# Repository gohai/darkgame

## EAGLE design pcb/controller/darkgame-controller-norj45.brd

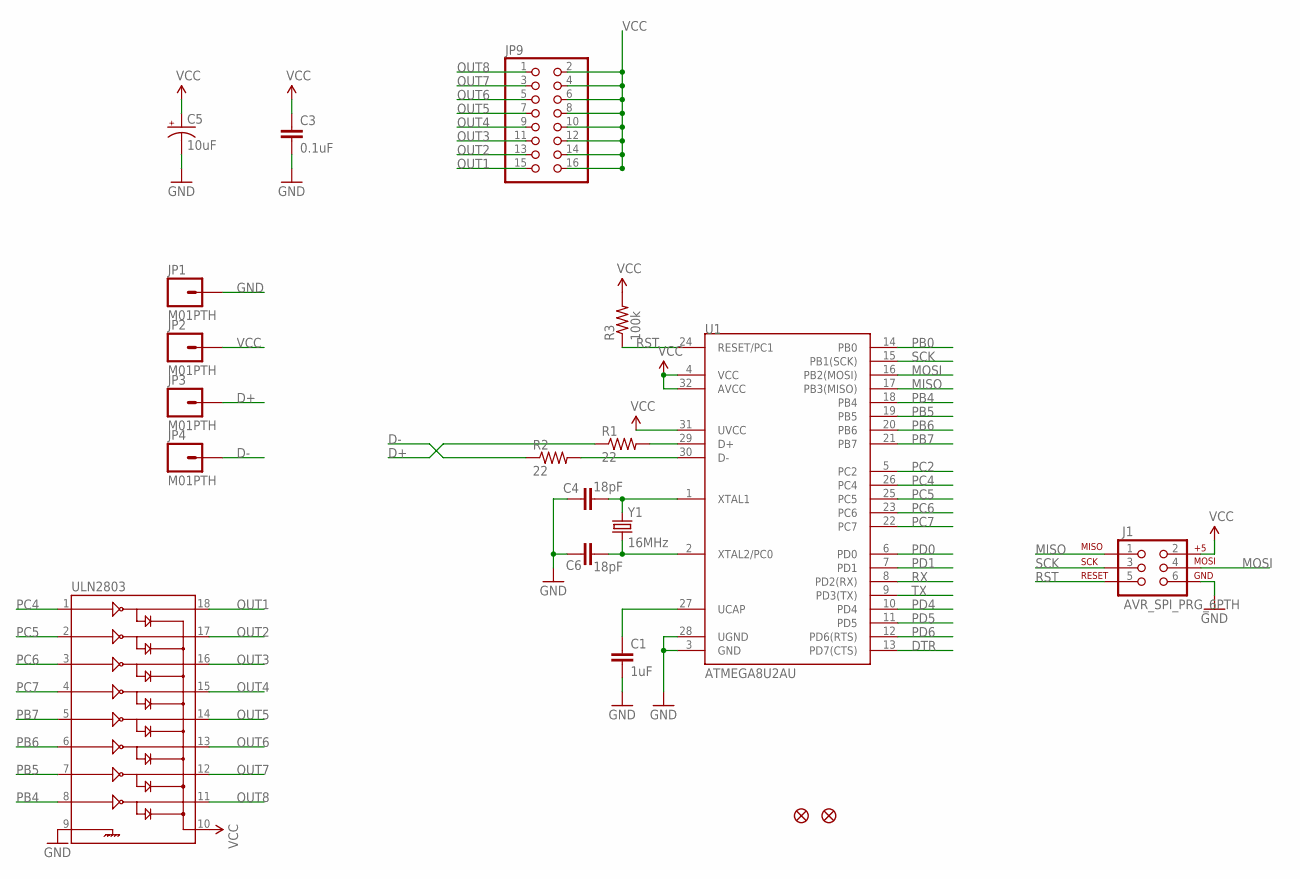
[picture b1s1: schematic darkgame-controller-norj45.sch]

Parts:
C1: 1uF; 0805
C3: 0.1uF; 0805
C4, C6: 18pF; 0805
C5: 10uF; EIA3216
J1: AVR_SPI_PRG_6PTH; 2X3
JP1, JP2, JP3, JP4: M01PTH; 1X01
JP6, JP7: FIDUCIAL1X2; FIDUCIAL-1X2
JP9: PINHD-2X8; 2X08
R1, R2: 22; 0805
R3: 100k; 0805
U1: ATMEGA8U2AU; TQFP32-08
ULN2803: ULN2803SOICW; SO18L
Y1: 16MHz; CRYSTAL-SMD-5X3

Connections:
D+: JP3.1, R1.1
D-: JP4.1, R2.1
DTR: U1.13 (PD7(CTS))
GND: C1.2, C3.2, C4.2, C5.C (-), C6.2, J1.6, JP1.1, U1.3 (GND), U1.28 (UGND), ULN2803.9
MISO: J1.1, U1.17 (PB3(MISO))
MOSI: J1.4, U1.16 (PB2(MOSI))
unnamed: R1.2, U1.29 (D+)
unnamed: R2.2, U1.30 (D-)
unnamed: C4.1, U1.1 (XTAL1), Y1.3 (2)
unnamed: C6.1, U1.2 (XTAL2/PC0), Y1.1
unnamed: C1.1, U1.27 (UCAP)
OUT1: JP9.15, ULN2803.18
OUT2: JP9.13, ULN2803.17
OUT3: JP9.11, ULN2803.16
OUT4: JP9.9, ULN2803.15
OUT5: JP9.7, ULN2803.14
OUT6: JP9.5, ULN2803.13
OUT7: JP9.3, ULN2803.12
OUT8: JP9.1, ULN2803.11
PB0: U1.14 (PB0)
PB4: U1.18 (PB4), ULN2803.8
PB5: U1.19 (PB5), ULN2803.7
PB6: U1.20 (PB6), ULN2803.6
PB7: U1.21 (PB7), ULN2803.5
PC2: U1.5 (PC2)
PC4: U1.26 (PC4), ULN2803.1
PC5: U1.25 (PC5), ULN2803.2
PC6: U1.23 (PC6), ULN2803.3
PC7: U1.22 (PC7), ULN2803.4
PD0: U1.6 (PD0)
PD1: U1.7 (PD1)
PD4: U1.10 (PD4)
PD5: U1.11 (PD5)
PD6: U1.12 (PD6(RTS))
RST: J1.5, R3.1, U1.24 (RESET/PC1)
RX: U1.8 (PD2(RX))
SCK: J1.3, U1.15 (PB1(SCK))
TX: U1.9 (PD3(TX))
VCC: C3.1, C5.A (+), J1.2, JP2.1, JP9.2, JP9.4, JP9.6, JP9.8, JP9.10, JP9.12, JP9.14, JP9.16, R3.2, U1.4 (VCC), U1.31 (UVCC), U1.32 (AVCC), ULN2803.10

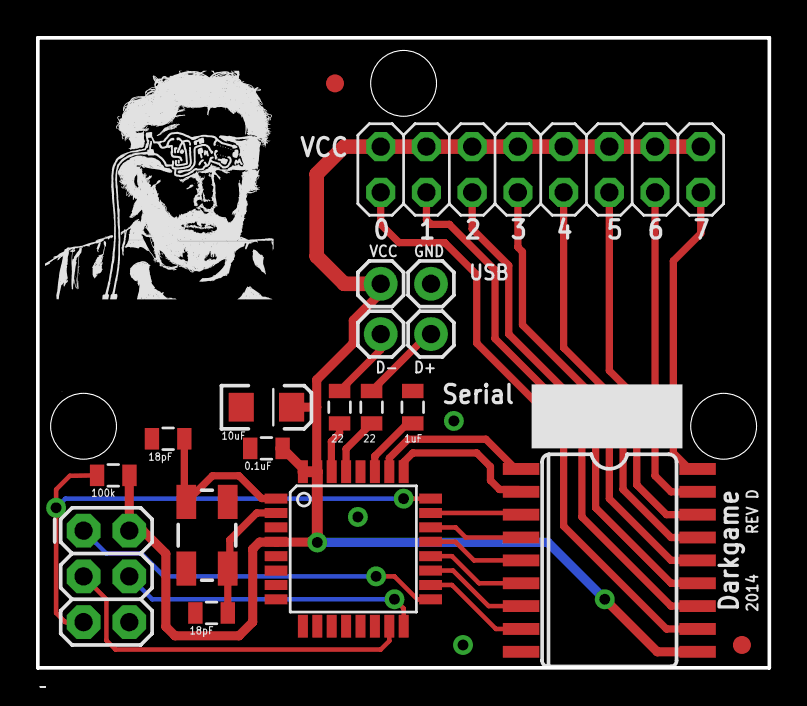
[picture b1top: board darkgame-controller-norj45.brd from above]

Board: 2 copper layers, 40.6 x 35.0 mm, 19 parts (0 on the bottom side), 29 nets.

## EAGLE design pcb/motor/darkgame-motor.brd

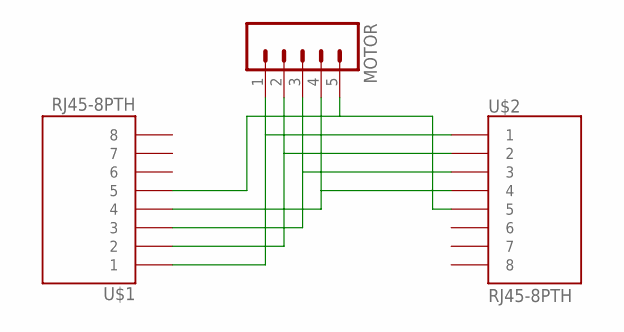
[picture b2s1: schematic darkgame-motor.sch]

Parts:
MOTOR: M05PTH; 1X05
U$1, U$2: RJ45-8PTH; RJ45-8

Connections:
unnamed: MOTOR.1, U$1.1, U$2.1
unnamed: MOTOR.2, U$1.2, U$2.2
unnamed: MOTOR.3, U$1.3, U$2.3
unnamed: MOTOR.4, U$1.4, U$2.4
unnamed: MOTOR.5, U$1.5, U$2.5

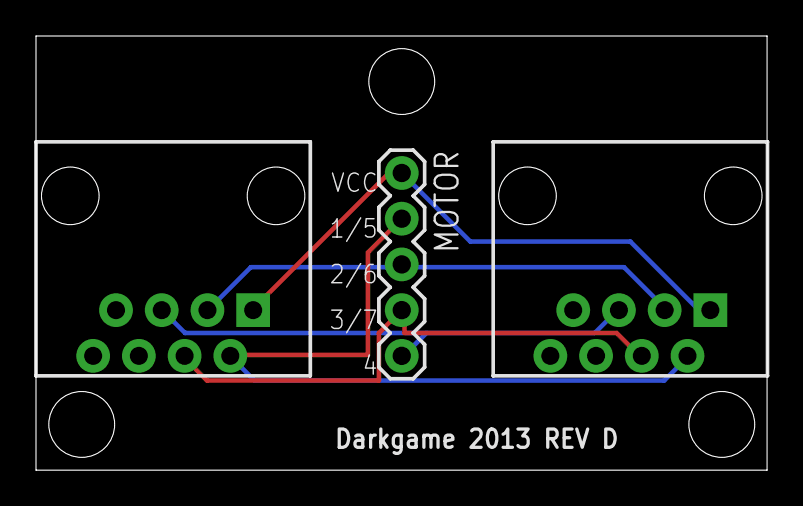
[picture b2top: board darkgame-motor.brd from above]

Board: 2 copper layers, 40.6 x 24.1 mm, 3 parts (0 on the bottom side), 5 nets.

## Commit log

2012-11-16 Rev C
2012-12-01 More todo
2012-12-21 Add USB ID information
2013-03-26 Use the vinyl cutter for the stencil Better document the assembly Move Serial number to a place on the board where it's actually visible
2013-03-26 Change file mode
2013-03-27 Remove demo firmware
2013-03-27 Change USB IDs Normalize line endings Remove demo firmware Remove temporary files Change file masks Add .gitignore
2013-03-27 Added avrdude directives to the Makefile
2013-03-27 More documentation updates
2013-03-27 Documentation updates
2013-03-27 Label changes Updated .gitignore
2013-03-28 More documentation changes
2013-04-05 Add link to AVR application note
2014-03-02 Update todo
2014-03-02 Add bitmask code (untested)
2014-03-02 Newly compiled firmware
2014-03-03 More Darkgame work
2014-03-17 Add a serial port selection to firmware test sketch
    Untested
2014-03-17 Add wiring diagram
2014-07-13 Add a new variant that uses regular male headers instead of Ethernet jacks

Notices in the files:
parts and their libraries:
SparkFun-PowerIC: Licensing: CC v3.0 Share-Alike You are welcome to use this library for commercial purposes.
